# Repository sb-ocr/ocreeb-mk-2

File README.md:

# Ocreeb MK2: Modular Macro Keyboard System 

Watch the build video ↓

Ocreeb MK2 is the second iteration of my macropad project. This version features the XIAO RP2040, supports hotswap sockets for the macropad, a detachable switch plate, an OLED screen, and magnetic external modules running the Seesaw firmware.

As I mentioned in the video, there are still major performance issues when using multiple external modules. This is probably due to my implementation of the shared interrupt, and I will look into it. 
Nevertheless, I will supplement this repo with all the files in case you ever wish to use a part of this.

Build instructions → [Instructables](https://www.instructables.com/Modular-Macro-Keyboard-System-Ocreeb-MK2/)

[![CC BY-NC-SA 4.0][cc-by-nc-sa-shield]][cc-by-nc-sa]

[![CC BY-NC-SA 4.0][cc-by-nc-sa-image]][cc-by-nc-sa]

[cc-by-nc-sa]: http://creativecommons.org/licenses/by-nc-sa/4.0/
[cc-by-nc-sa-image]: https://licensebuttons.net/l/by-nc-sa/4.0/88x31.png
[cc-by-nc-sa-shield]: https://img.shields.io/badge/License-CC%20BY--NC--SA%204.0-lightgrey.svg

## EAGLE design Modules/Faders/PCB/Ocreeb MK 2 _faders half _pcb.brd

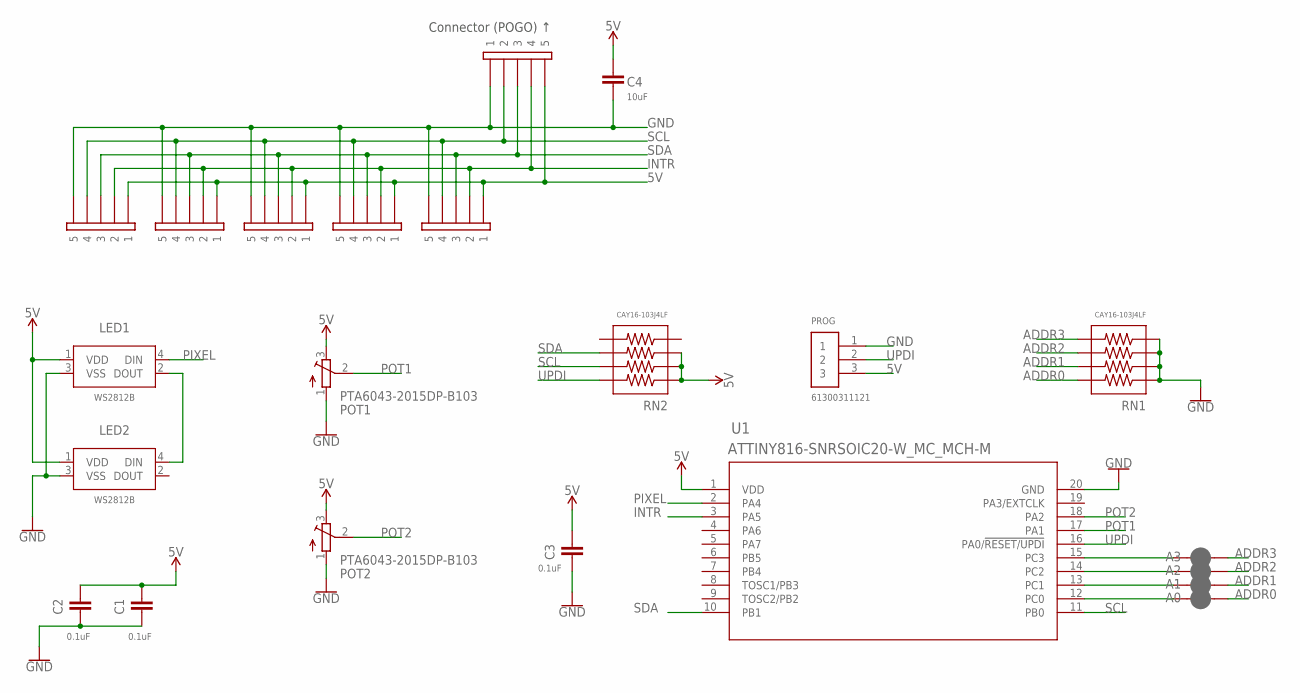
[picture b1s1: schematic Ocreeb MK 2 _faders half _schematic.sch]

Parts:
A0, A1, A2, A3: JUMPER-SMT_2_NC_PASTE_SILK; SMT-JUMPER_2_NC_PASTE_SILK
C1, C2, C3: 0.1uF; CAPC1608X85
C4: 10uF; CAPC2012X110
LED1, LED2: WS2812B
POT1, POT2: PTA6043-2015DP-B103
PROG: 61300311121
RN1, RN2: CAY16-103J4LF; RESCAF80P320X160X60-8N
U1: ATTINY816-SNRSOIC20-W_MC_MCH-M; SOIC20-W_MC_MCH-M
U$1: 5PIN_EDGE5_POGO_EDGE_OUT_; 5_POGO_EDGE
U$2, U$3, U$4, U$5, U$6: 5PIN_EDGE; 5_POGO_EDGE

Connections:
5V: C1.2, C2.2, C3.2, C4.2, LED1.1 (VDD), LED2.1 (VDD), POT1.3, POT2.3, PROG.3, RN2.1, RN2.2, RN2.3, U1.1 (VDD), U$1.5, U$2.1, U$3.1, U$4.1, U$5.1, U$6.1
ADDR0: A0.1, RN1.8
ADDR1: A1.1, RN1.7
ADDR2: A2.1, RN1.6
ADDR3: A3.1, RN1.5
GND: C1.1, C2.1, C3.1, C4.1, LED1.3 (VSS), LED2.3 (VSS), POT1.1, POT2.1, PROG.1, RN1.1, RN1.2, RN1.3, RN1.4, U1.20 (GND), U$1.1, U$2.5, U$3.5, U$4.5, U$5.5, U$6.5
INTR: U1.3 (PA5), U$1.4, U$2.2, U$3.2, U$4.2, U$5.2, U$6.2
unnamed: LED1.2 (DOUT), LED2.4 (DIN)
unnamed: A3.2, U1.15 (PC3)
unnamed: A2.2, U1.14 (PC2)
unnamed: A1.2, U1.13 (PC1)
unnamed: A0.2, U1.12 (PC0)
PIXEL: LED1.4 (DIN), U1.2 (PA4)
POT1: POT1.2, U1.17 (PA1)
POT2: POT2.2, U1.18 (PA2)
SCL: RN2.7, U1.11 (PB0), U$1.2, U$2.4, U$3.4, U$4.4, U$5.4, U$6.4
SDA: RN2.6, U1.10 (PB1), U$1.3, U$2.3, U$3.3, U$4.3, U$5.3, U$6.3
UPDI: PROG.2, RN2.8, U1.16 (PA0/!RESET/UPDI)

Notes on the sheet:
Connector (POGO) ↑

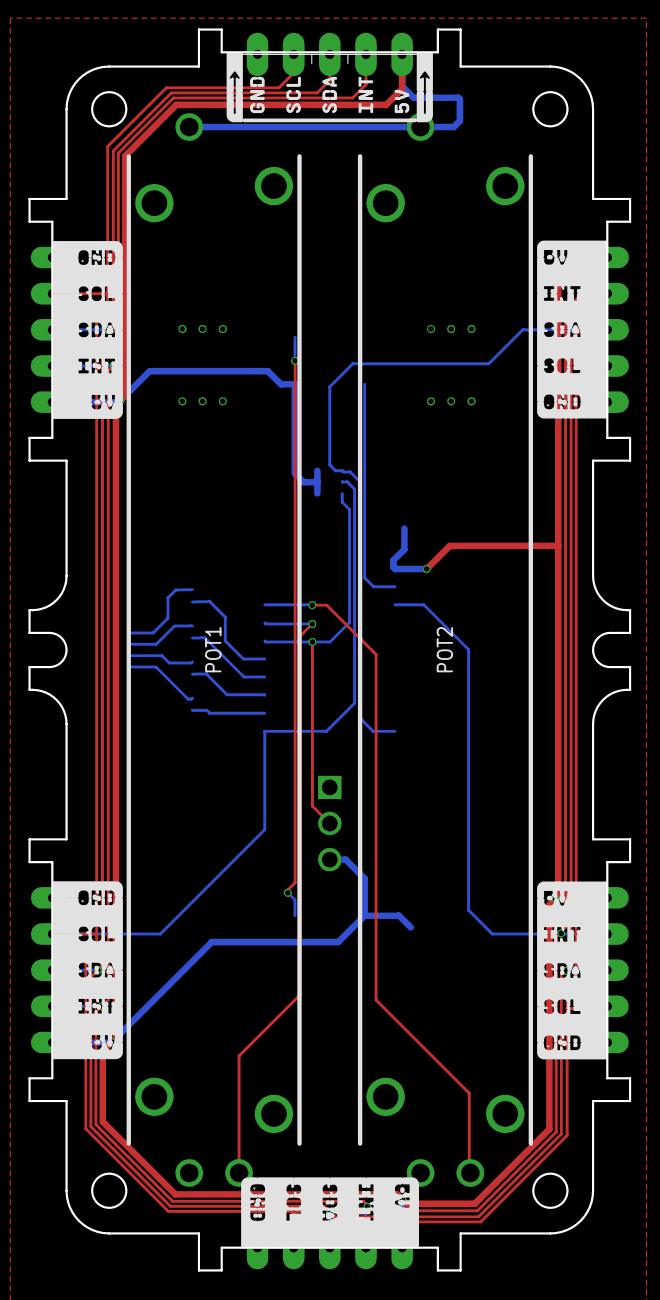
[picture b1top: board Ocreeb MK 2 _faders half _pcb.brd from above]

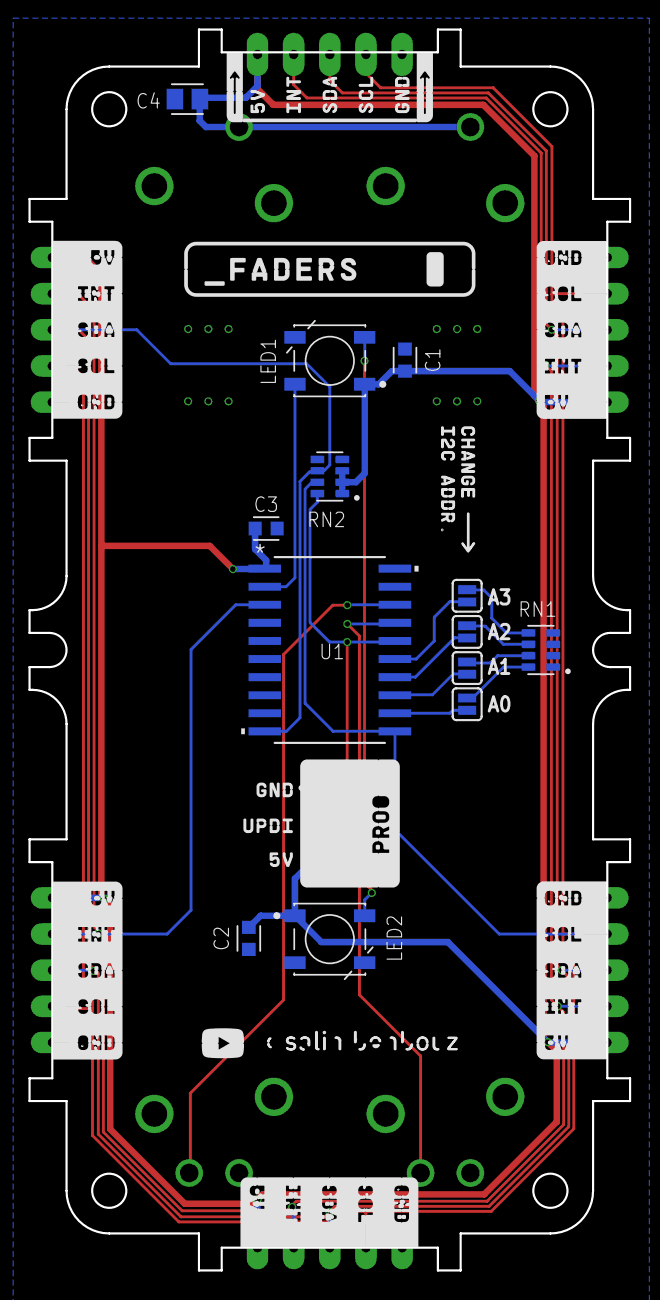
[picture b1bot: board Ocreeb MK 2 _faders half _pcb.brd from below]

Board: 2 copper layers, 42.2 x 87.2 mm, 22 parts (14 on the bottom side), 18 nets.

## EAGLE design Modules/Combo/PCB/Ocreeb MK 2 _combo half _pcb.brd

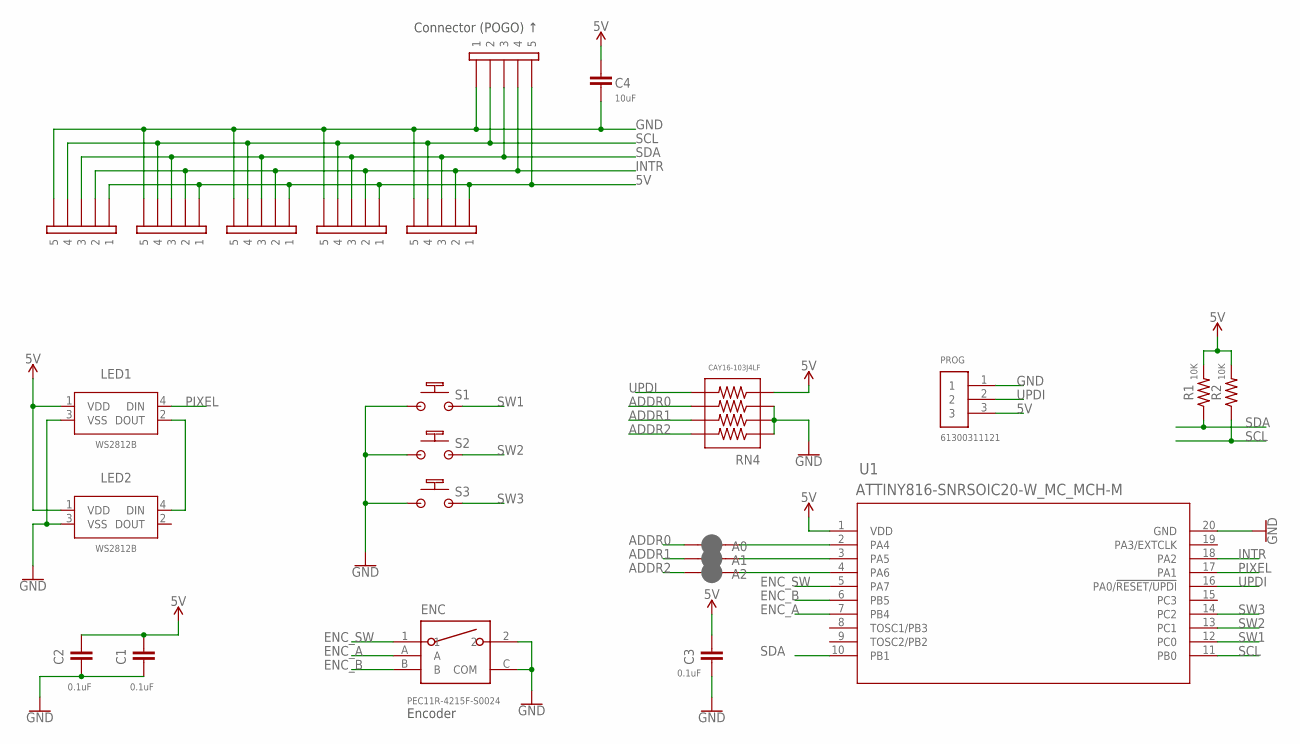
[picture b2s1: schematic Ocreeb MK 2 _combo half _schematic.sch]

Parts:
A0, A1, A2: JUMPER-SMT_2_NC_PASTE_SILK; SMT-JUMPER_2_NC_PASTE_SILK
C1, C2, C3: 0.1uF; CAPC1608X85
C4: 10uF; CAPC2012X110
ENC: PEC11R-4215F-S0024
LED1, LED2: WS2812B
PROG: 61300311121
R1, R2: 10K; RESC1608X60
RN4: CAY16-103J4LF; RESCAF80P320X160X60-8N
S1, S2, S3: MX1A-11NNCHERRY_MX_SOLDER; CHERRY_MX1A-11NN_SWITCH_NO_HOTSWAP
U1: ATTINY816-SNRSOIC20-W_MC_MCH-M; SOIC20-W_MC_MCH-M
U$1: 5PIN_EDGE5_POGO_EDGE_OUT_; 5_POGO_EDGE
U$2, U$3, U$4, U$5, U$6: 5PIN_EDGE; 5_POGO_EDGE

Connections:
5V: C1.2, C2.2, C3.2, C4.2, LED1.1 (VDD), LED2.1 (VDD), PROG.3, R1.2, R2.2, RN4.4, U1.1 (VDD), U$1.5, U$2.1, U$3.1, U$4.1, U$5.1, U$6.1
ADDR0: A0.1, RN4.6
ADDR1: A1.1, RN4.7
ADDR2: A2.1, RN4.8
ENC_A: ENC.A, U1.7 (PB4)
ENC_B: ENC.B, U1.6 (PB5)
ENC_SW: ENC.1, U1.5 (PA7)
GND: C1.1, C2.1, C3.1, C4.1, ENC.2, ENC.C (COM), LED1.3 (VSS), LED2.3 (VSS), PROG.1, RN4.1, RN4.2, RN4.3, S1.1_ALT (1), S2.1_ALT (1), S3.1_ALT (1), U1.20 (GND), U$1.1, U$2.5, U$3.5, U$4.5, U$5.5, U$6.5
INTR: U1.18 (PA2), U$1.4, U$2.2, U$3.2, U$4.2, U$5.2, U$6.2
unnamed: LED1.2 (DOUT), LED2.4 (DIN)
unnamed: A0.2, U1.2 (PA4)
unnamed: A1.2, U1.3 (PA5)
unnamed: A2.2, U1.4 (PA6)
PIXEL: LED1.4 (DIN), U1.17 (PA1)
SCL: R2.1, U1.11 (PB0), U$1.2, U$2.4, U$3.4, U$4.4, U$5.4, U$6.4
SDA: R1.1, U1.10 (PB1), U$1.3, U$2.3, U$3.3, U$4.3, U$5.3, U$6.3
SW1: S1.2_ALT (2), U1.12 (PC0)
SW2: S2.2_ALT (2), U1.13 (PC1)
SW3: S3.2_ALT (2), U1.14 (PC2)
UPDI: PROG.2, RN4.5, U1.16 (PA0/!RESET/UPDI)

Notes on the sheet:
Encoder
Connector (POGO) ↑

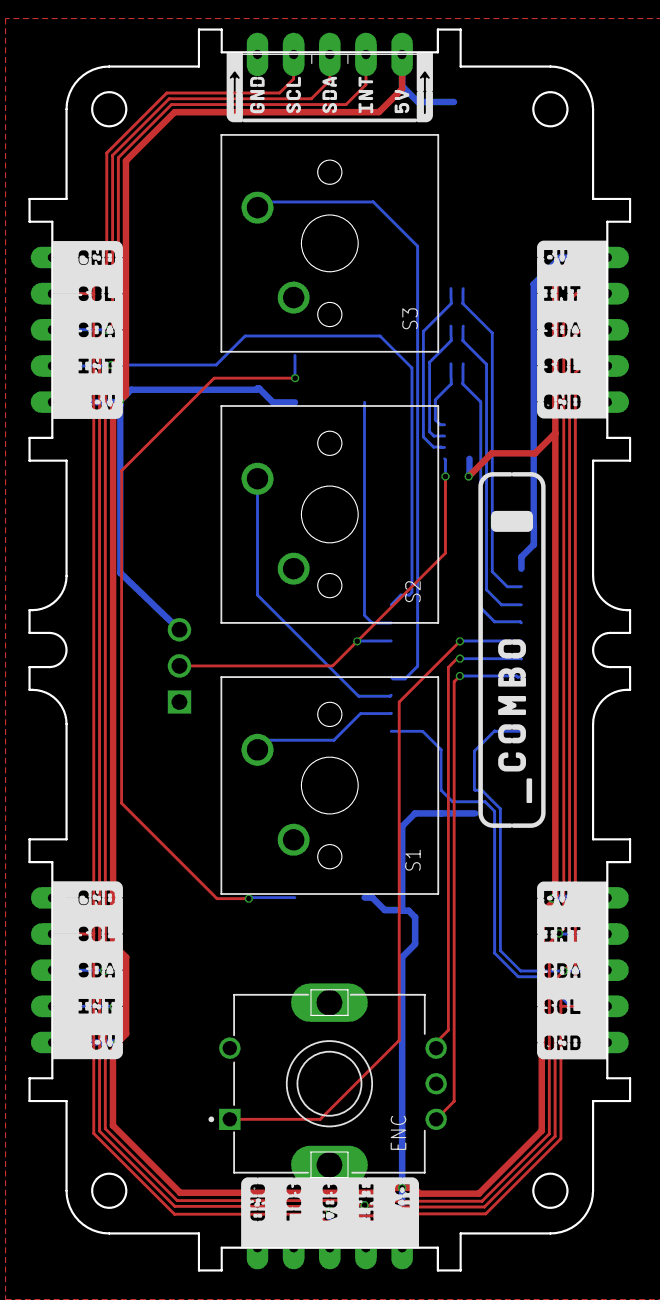
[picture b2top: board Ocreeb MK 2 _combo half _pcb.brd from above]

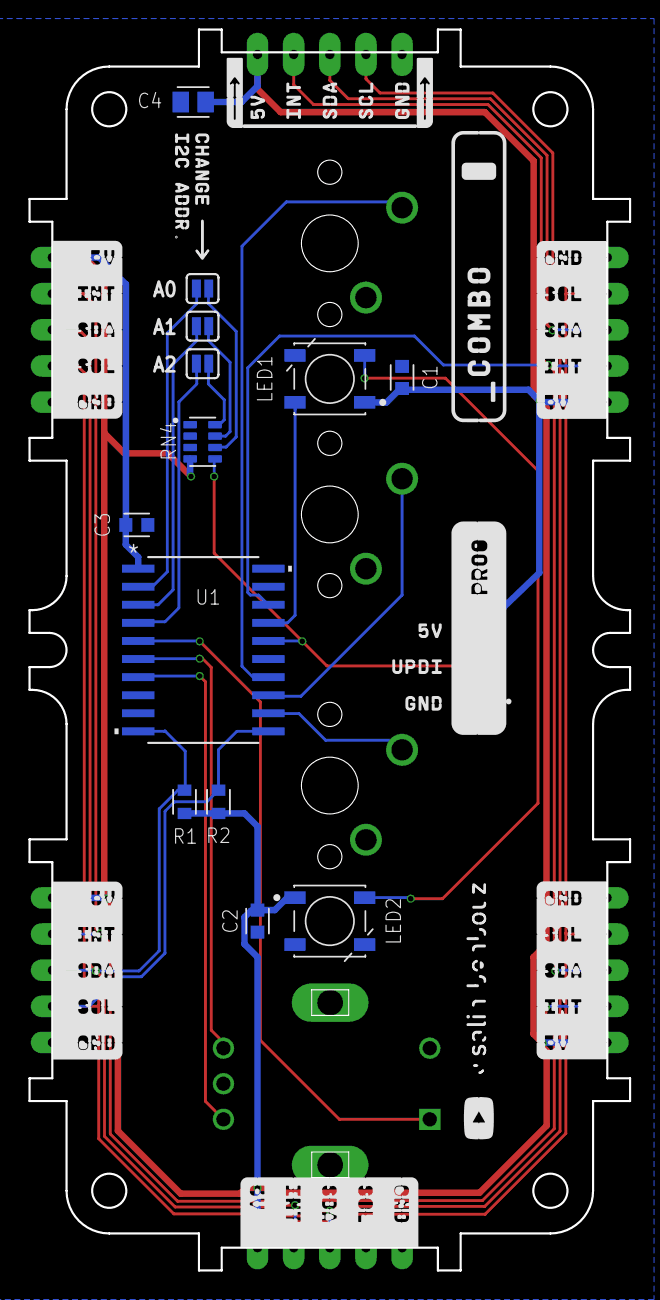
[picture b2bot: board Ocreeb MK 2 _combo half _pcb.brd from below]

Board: 2 copper layers, 42.2 x 87.2 mm, 24 parts (14 on the bottom side), 20 nets.

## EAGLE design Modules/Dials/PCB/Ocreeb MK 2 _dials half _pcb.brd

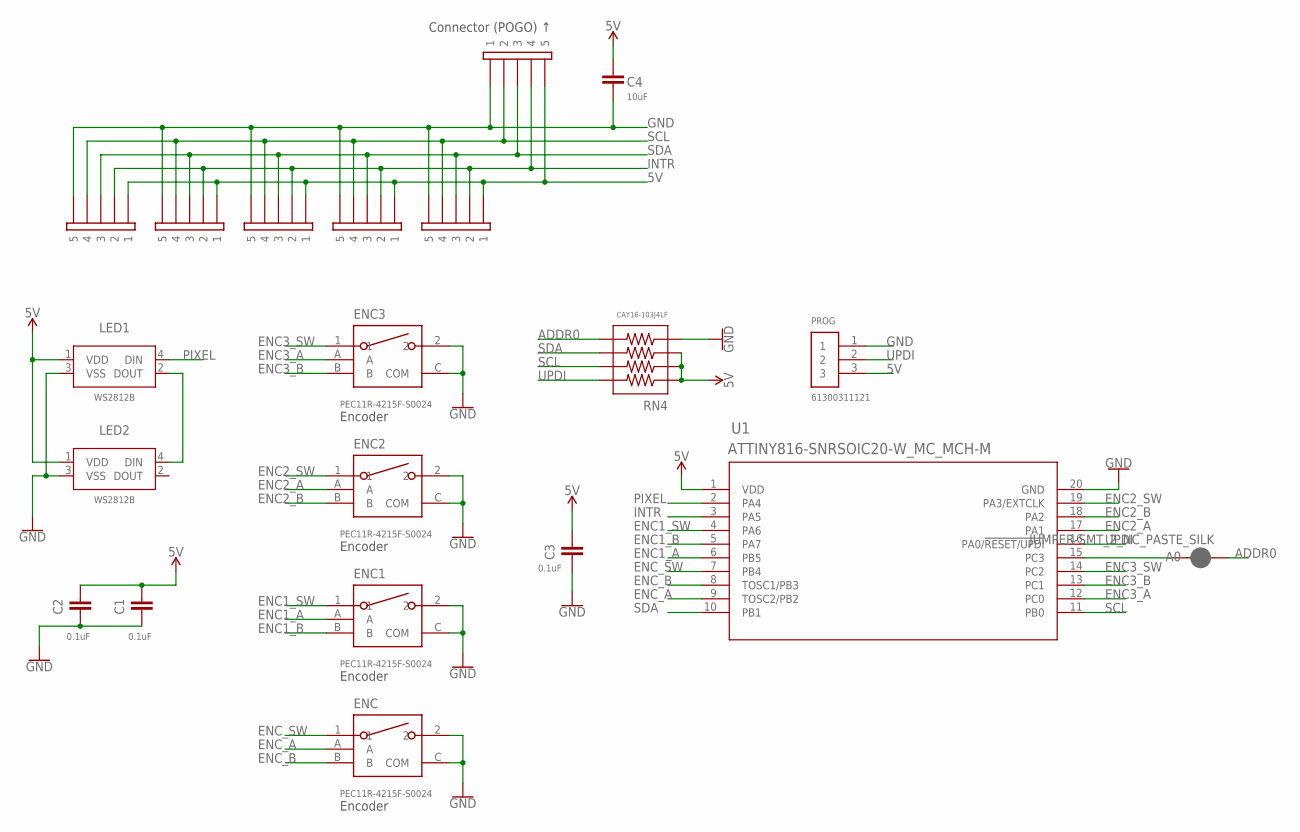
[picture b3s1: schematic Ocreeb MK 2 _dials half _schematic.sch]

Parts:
A0: JUMPER-SMT_2_NC_PASTE_SILK; SMT-JUMPER_2_NC_PASTE_SILK
C1, C2, C3: 0.1uF; CAPC1608X85
C4: 10uF; CAPC2012X110
ENC, ENC1, ENC2, ENC3: PEC11R-4215F-S0024
LED1, LED2: WS2812B
PROG: 61300311121
RN4: CAY16-103J4LF; RESCAF80P320X160X60-8N
U1: ATTINY816-SNRSOIC20-W_MC_MCH-M; SOIC20-W_MC_MCH-M
U$1: 5PIN_EDGE5_POGO_EDGE_OUT_; 5_POGO_EDGE
U$2, U$3, U$4, U$5, U$6: 5PIN_EDGE; 5_POGO_EDGE

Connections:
5V: C1.2, C2.2, C3.2, C4.2, LED1.1 (VDD), LED2.1 (VDD), PROG.3, RN4.1, RN4.2, RN4.3, U1.1 (VDD), U$1.5, U$2.1, U$3.1, U$4.1, U$5.1, U$6.1
ADDR0: A0.1, RN4.5
ENC1_A: ENC1.A, U1.6 (PB5)
ENC1_B: ENC1.B, U1.5 (PA7)
ENC1_SW: ENC1.1, U1.4 (PA6)
ENC2_A: ENC2.A, U1.17 (PA1)
ENC2_B: ENC2.B, U1.18 (PA2)
ENC2_SW: ENC2.1, U1.19 (PA3/EXTCLK)
ENC3_A: ENC3.A, U1.12 (PC0)
ENC3_B: ENC3.B, U1.13 (PC1)
ENC3_SW: ENC3.1, U1.14 (PC2)
ENC_A: ENC.A, U1.9 (TOSC2/PB2)
ENC_B: ENC.B, U1.8 (TOSC1/PB3)
ENC_SW: ENC.1, U1.7 (PB4)
GND: C1.1, C2.1, C3.1, C4.1, ENC.2, ENC.C (COM), ENC1.2, ENC1.C (COM), ENC2.2, ENC2.C (COM), ENC3.2, ENC3.C (COM), LED1.3 (VSS), LED2.3 (VSS), PROG.1, RN4.4, U1.20 (GND), U$1.1, U$2.5, U$3.5, U$4.5, U$5.5, U$6.5
INTR: U1.3 (PA5), U$1.4, U$2.2, U$3.2, U$4.2, U$5.2, U$6.2
unnamed: LED1.2 (DOUT), LED2.4 (DIN)
unnamed: A0.2, U1.15 (PC3)
PIXEL: LED1.4 (DIN), U1.2 (PA4)
SCL: RN4.7, U1.11 (PB0), U$1.2, U$2.4, U$3.4, U$4.4, U$5.4, U$6.4
SDA: RN4.6, U1.10 (PB1), U$1.3, U$2.3, U$3.3, U$4.3, U$5.3, U$6.3
UPDI: PROG.2, RN4.8, U1.16 (PA0/!RESET/UPDI)

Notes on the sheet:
Encoder
Connector (POGO) ↑

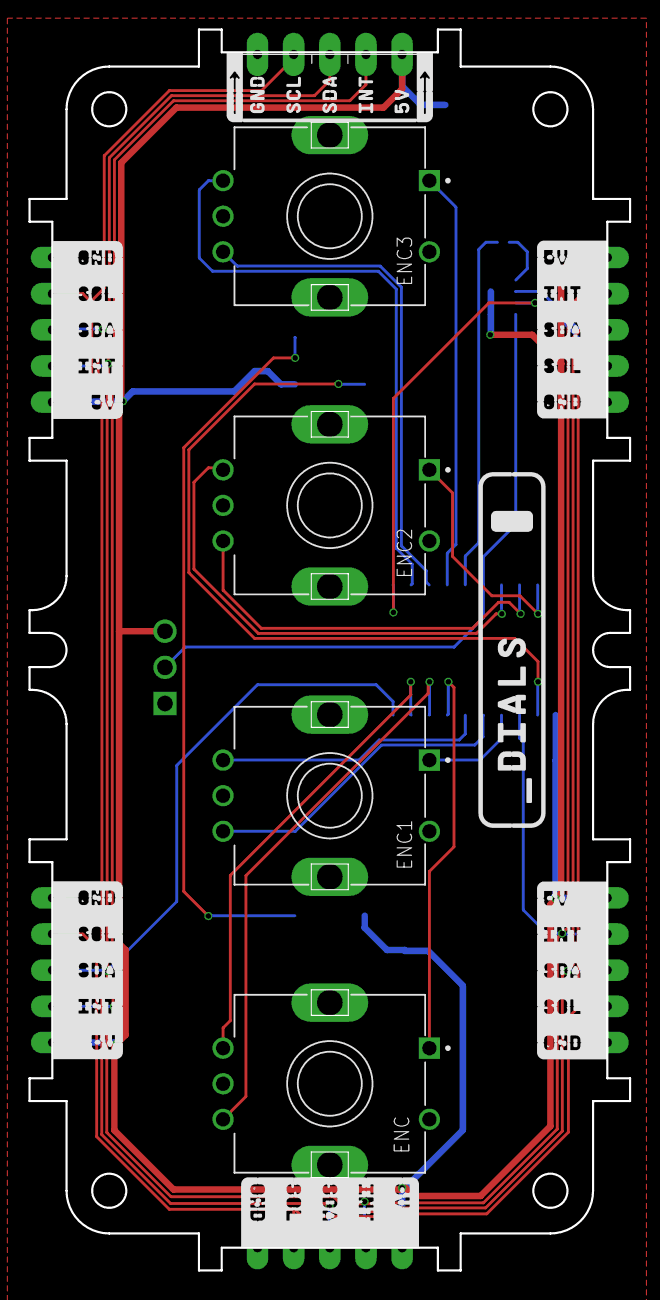
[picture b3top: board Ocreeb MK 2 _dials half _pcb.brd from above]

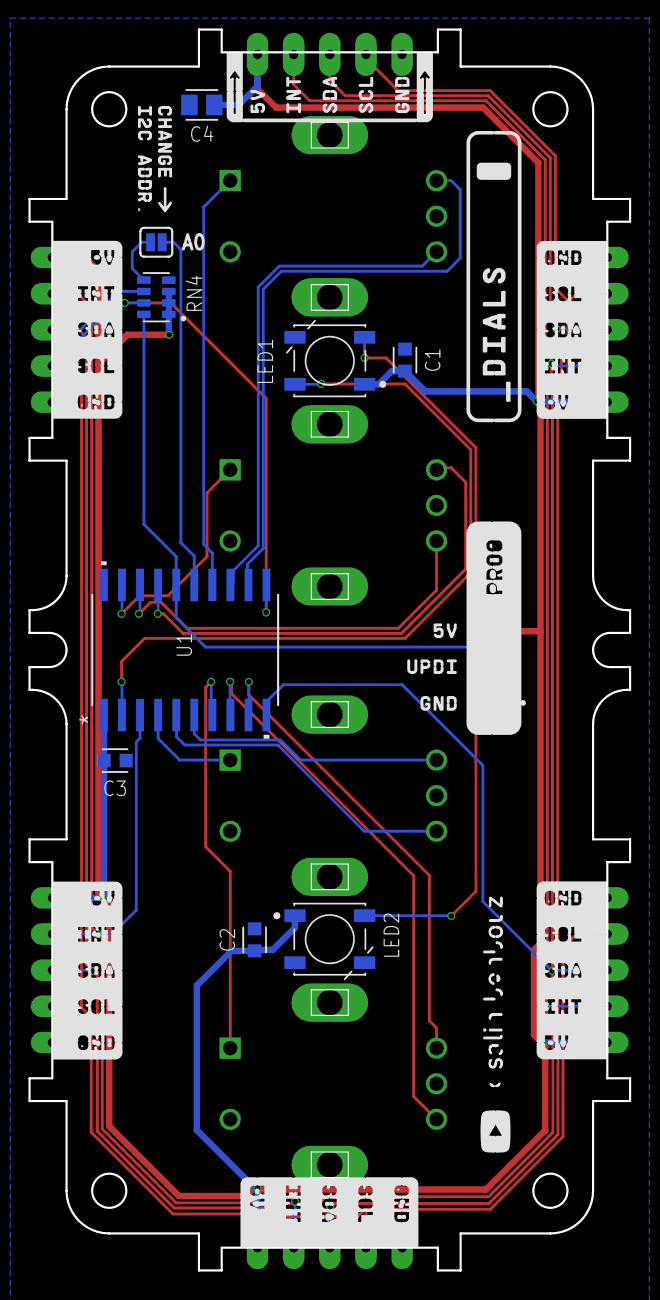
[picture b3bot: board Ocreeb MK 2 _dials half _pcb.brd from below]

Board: 2 copper layers, 42.2 x 87.2 mm, 20 parts (10 on the bottom side), 22 nets.

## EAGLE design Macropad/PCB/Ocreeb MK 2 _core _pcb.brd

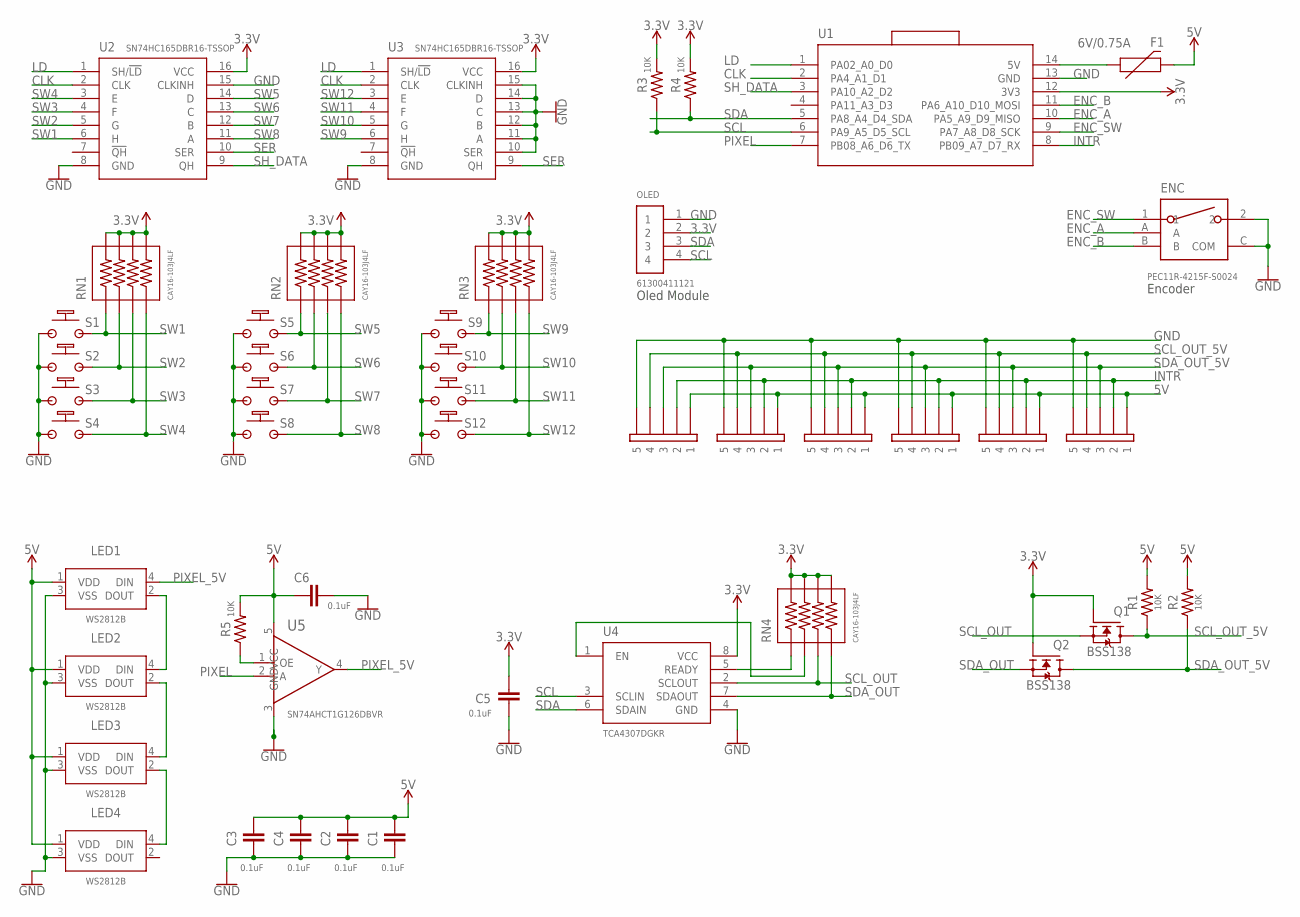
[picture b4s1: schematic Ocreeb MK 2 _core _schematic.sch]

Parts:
C1, C2, C3, C4, C5, C6: 0.1uF; CAPC1608X85
ENC: PEC11R-4215F-S0024
F1: 6V/0.75A; 1206
LED1, LED2, LED3, LED4: WS2812B
OLED: 61300411121
Q1, Q2: BSS138; SOT95P240X111-3N
R1, R2, R3, R4, R5: 10K; RESC1608X60
RN1, RN2, RN3, RN4: CAY16-103J4LF; RESCAF80P320X160X60-8N
S1, S2, S3, S4, S5, S6, S7, S8, S9, S10, S11, S12: MX1A-11NN; CHERRY_MX1A-11NN_SWITCH
U1: MOUDLE-SEEEDUINO-XIAO-SMD; MOUDLE14P-SMD-2.54-21X17.8MM
U2, U3: SN74HC165DBR16-TSSOP; SOP65P640X120-16N
U4: TCA4307DGKR; SOP65P490X110-8N
U5: SN74AHCT1G126DBVR; SOT95P280X145-5N
U$1, U$2, U$3, U$4, U$5, U$6: 5PIN_EDGE; 5_POGO_EDGE

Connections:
3.3V: C5.2, OLED.2, Q1.1 (G), Q2.1 (G), R3.2, R4.2, RN1.5, RN1.6, RN1.7, RN1.8, RN2.5, RN2.6, RN2.7, RN2.8, RN3.5, RN3.6, RN3.7, RN3.8, RN4.5, RN4.6, RN4.7, RN4.8, U1.12 (3V3), U2.16 (VCC), U3.16 (VCC), U4.8 (VCC)
5V: C1.2, C2.2, C3.2, C4.2, C6.2, F1.2, LED1.1 (VDD), LED2.1 (VDD), LED3.1 (VDD), LED4.1 (VDD), R1.2, R2.2, R5.2, U5.5 (VCC), U$1.1, U$2.1, U$3.1, U$4.1, U$5.1, U$6.1
CLK: U1.2 (PA4_A1_D1), U2.2 (CLK), U3.2 (CLK)
ENC_A: ENC.A, U1.10 (PA5_A9_D9_MISO)
ENC_B: ENC.B, U1.11 (PA6_A10_D10_MOSI)
ENC_SW: ENC.1, U1.9 (PA7_A8_D8_SCK)
GND: C1.1, C2.1, C3.1, C4.1, C5.1, C6.1, ENC.2, ENC.C (COM), LED1.3 (VSS), LED2.3 (VSS), LED3.3 (VSS), LED4.3 (VSS), OLED.1, S1.1, S1.1_ALT (1), S2.1, S2.1_ALT (1), S3.1, S3.1_ALT (1), S4.1, S4.1_ALT (1), S5.1, S5.1_ALT (1), S6.1, S6.1_ALT (1), S7.1, S7.1_ALT (1), S8.1, S8.1_ALT (1), S9.1, S9.1_ALT (1), S10.1, S10.1_ALT (1), S11.1, S11.1_ALT (1), S12.1, S12.1_ALT (1), U1.13 (GND), U2.8 (GND), U2.15 (CLKINH), U3.8 (GND), U3.10 (SER), U3.11 (A), U3.12 (B), U3.13 (C), U3.14 (D), U3.15 (CLKINH), U4.4 (GND), U5.3 (GND), U$1.5, U$2.5, U$3.5, U$4.5, U$5.5, U$6.5
INTR: U1.8 (PB09_A7_D7_RX), U$1.2, U$2.2, U$3.2, U$4.2, U$5.2, U$6.2
LD: U1.1 (PA02_A0_D0), U2.1 (SH/!LD), U3.1 (SH/!LD)
unnamed: RN4.1, U4.5 (READY)
unnamed: R5.1, U5.1 (OE)
unnamed: LED1.2 (DOUT), LED2.4 (DIN)
unnamed: LED2.2 (DOUT), LED3.4 (DIN)
unnamed: LED3.2 (DOUT), LED4.4 (DIN)
unnamed: RN4.2, U4.1 (EN)
PIXEL: U1.7 (PB08_A6_D6_TX), U5.2 (A)
PIXEL_5V: LED1.4 (DIN), U5.4 (Y)
SCL: OLED.4, R3.1, U1.6 (PA9_A5_D5_SCL), U4.3 (SCLIN)
SCL_OUT: Q1.2 (S), RN4.3, U4.2 (SCLOUT)
SCL_OUT_5V: Q1.3 (D), R1.1, U$1.4, U$2.4, U$3.4, U$4.4, U$5.4, U$6.4
SDA: OLED.3, R4.1, U1.5 (PA8_A4_D4_SDA), U4.6 (SDAIN)
SDA_OUT: Q2.2 (S), RN4.4, U4.7 (SDAOUT)
SDA_OUT_5V: Q2.3 (D), R2.1, U$1.3, U$2.3, U$3.3, U$4.3, U$5.3, U$6.3
SER: U2.10 (SER), U3.9 (QH)
SH_DATA: U1.3 (PA10_A2_D2), U2.9 (QH)
SW1: RN1.1, S1.2, S1.2_ALT (2), U2.6 (H)
SW2: RN1.2, S2.2, S2.2_ALT (2), U2.5 (G)
SW3: RN1.3, S3.2, S3.2_ALT (2), U2.4 (F)
SW4: RN1.4, S4.2, S4.2_ALT (2), U2.3 (E)
SW5: RN2.1, S5.2, S5.2_ALT (2), U2.14 (D)
SW6: RN2.2, S6.2, S6.2_ALT (2), U2.13 (C)
SW7: RN2.3, S7.2, S7.2_ALT (2), U2.12 (B)
SW8: RN2.4, S8.2, S8.2_ALT (2), U2.11 (A)
SW9: RN3.1, S9.2, S9.2_ALT (2), U3.6 (H)
SW10: RN3.2, S10.2, S10.2_ALT (2), U3.5 (G)
SW11: RN3.3, S11.2, S11.2_ALT (2), U3.4 (F)
SW12: RN3.4, S12.2, S12.2_ALT (2), U3.3 (E)
USB_5V: F1.1, U1.14 (5V)

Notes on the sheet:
Oled Module
Encoder

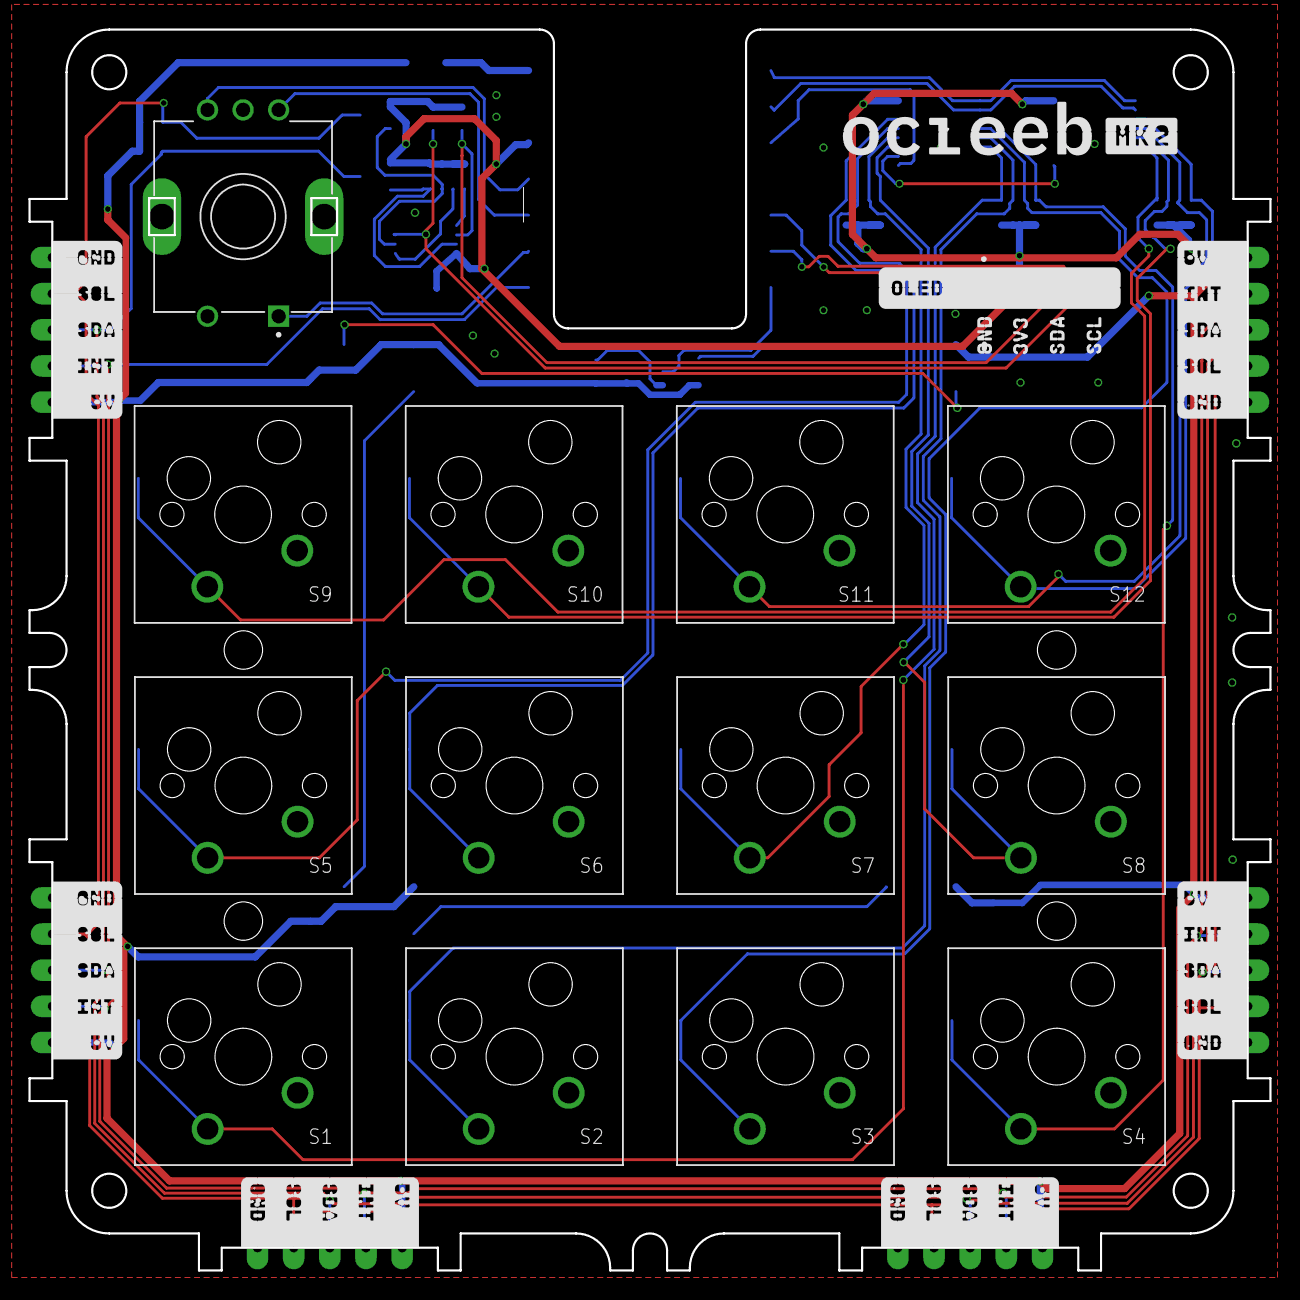
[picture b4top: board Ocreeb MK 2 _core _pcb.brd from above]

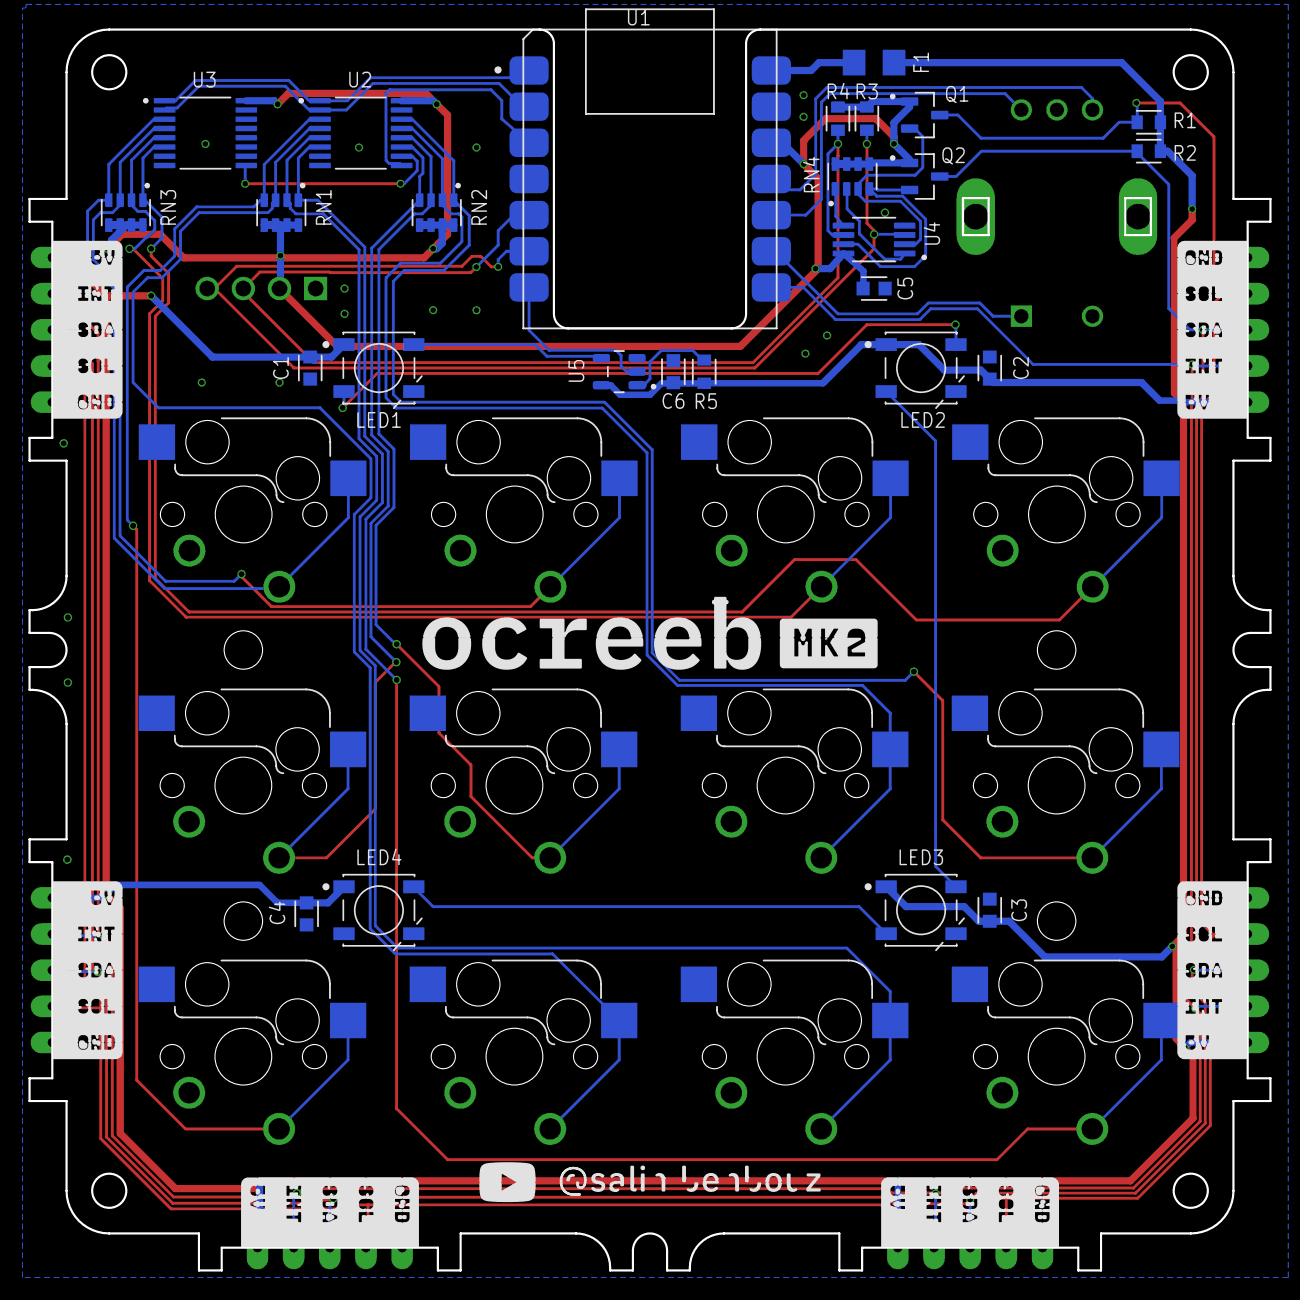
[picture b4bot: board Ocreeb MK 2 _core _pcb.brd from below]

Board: 2 copper layers, 87.2 x 87.2 mm, 47 parts (27 on the bottom side), 38 nets.

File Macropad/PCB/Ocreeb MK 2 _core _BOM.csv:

Qty,Parts,Device,Value,Package,MP,Digikey,Type,Description,Link
1,U1,XIAO RP2040,,,102010428,1597-102010428-ND,SMD,RP2040 XIAO RP2040 - ARM® Cortex®-M0+ MCU 32-Bit,
6,"C1, C2, C3, C4, C5, C6",C_CHIP-0603(1608-METRIC),0.1uF,CAPC1608X85,C0603C104M5RAC7867,399-C0603C104M5RAC7867CT-ND,SMD,0.1 µF ±20% 50V Ceramic Capacitor X7R 0603 (1608 Metric),
5,"R1, R2, R3, R4, R5",R-US_CHIP-0603(1608-METRIC),10K,RESC1608X60,RMCF0603FT10K0,RMCF0603FT10K0CT-ND,SMD,"10 kOhms ±1% 0.1W, 1/10W Chip Resistor 0603 (1608 Metric)",
1,F1,PPTC_0.75A,6V/0.75A,1206 (3216 Metric),PTS12066V075,283-PTS12066V075CT-ND,SMD,"Polymeric PTC Resettable Fuse 6V 750 mA Ih Surface Mount 1206 (3216 Metric), Concave",
2,"Q1, Q2",BSS138,BSS138,SOT-23-3,BSS138,4530-BSS138CT-ND,SMD,N-Channel 50 V 220mA (Ta) 350mW (Ta) Surface Mount SOT-23,
4,"RN1, RN2, RN3, RN4",CAY16-103J4LF,CAY16-103J4LF,1206 (3216 Metric),CAY16-103J4LF,CAY16-103J4LFCT-ND,SMD,"10k Ohm ±5% 62.5mW Power Per Element Isolated 4 Resistor Network/Array ±200ppm/°C 1206 (3216 Metric), Convex, Long Side Terminals",
1,U5,SN74AHCT1G126DBVR,SN74AHCT1G126DBVR,SOT-23-5,SN74AHCT1G126DBVR,296-4710-1-ND,SMD,"Buffer, Non-Inverting 1 Element 1 Bit per Element 3-State Output SOT-23-5",
2,"U2, U3",SN74HC165DBR16-TSSOP,SN74HC165DBR16-TSSOP,16-SSOP,SN74HC165DBR,296-23151-1-ND,SMD,Shift Shift Register 1 Element 8 Bit 16-SSOP,
1,U4,TCA4307DGKR,TCA4307DGKR,8-VSSOP,TCA4307DGKR,296-TCA4307DGKRCT-ND,SMD,Hot Swap Controller 1 Channel General Purpose 8-VSSOP,
4,"LED1, LED2, LED3, LED4",WS2812B,WS2812B,WS2812B,COM-16347,1568-COM-16347CT-ND,SMD,"Addressable Lighting - LED Serial NRZ (Shift Register) Red, Green, Blue (RGB)",
1,ENC,PEC11R-4215F-S0024,PEC11R-4215F-S0024,PEC11R-4215F-S0024,PEC11R-4215F-S0024,PEC11R-4215F-S0024-ND,TH,Rotary Encoder Mechanical 24 Quadrature (Incremental) Vertical,
12,"S1, S2, S3, S4, S5, S6, S7, S8, S9, S10, S11, S12",MX HOT SWAP SOCKETS,,20 Pack,4958,1528-4958-ND,SMD,Kailh MX Hotswap Sockets,
12,"S1, S2, S3, S4, S5, S6, S7, S8, S9, S10, S11, S12",MX SWITCHES,,12 Pack,5122,1528-5122-ND,TH,MX-Compatible Mechanical Keys,
1,OLED,OLED MODULE,,3 pcs,,,MOD,0.91 inch OLED Display Module SSD1306 I2C 128x32,https://geni.us/Jc6463D
6,CONNECTOR,5PIN_EDGE_LANDING,,5 pcs,,,SUB,Custom landing pads PCB,https://github.com/sb-ocr/ocreeb-mk-2/tree/main/Connector/PC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
4,SCR,M2 x 6mm,,Assorted Lengths Kit,,,SCR,M2 Self-Tapping Screws,https://geni.us/OKq551
3,SCR,M2 x 12mm,,Assorted Lengths Kit,,,SCR,M2 Self-Tapping Screws,https://geni.us/OKq551
4,SCR,M2 x 16mm,,Assorted Lengths Kit,,,SCR,M2 Self-Tapping Screws,https://geni.us/OKq551
12,MAG,6 x 3mm,,40 pcs,,,MAG,Small Neodymium Magnets,https://geni.us/X7I9
4,ADH,6 x 2 mm,,Assorted Kit,,,ADH,Adhesive Bumper Pads Self Stick,https://geni.us/v9UIrL

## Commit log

2024-01-15 YT-upload
2024-01-18 License
2024-01-22 BOMs sup. and Step files
2024-02-04 Schematics + keycap STL
2024-02-04 Eagle sch + brd files

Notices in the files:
parts and their libraries:
SparkFun-Fuses: Licensing: Creative Commons ShareAlike 4.0 International - https://creativecommons.org/licenses/by-sa/4.0
ul_SN74HC165DBR: COPYRIGHT: Copyright (C) 2023 Ultra Librarian. All rights reserved.
